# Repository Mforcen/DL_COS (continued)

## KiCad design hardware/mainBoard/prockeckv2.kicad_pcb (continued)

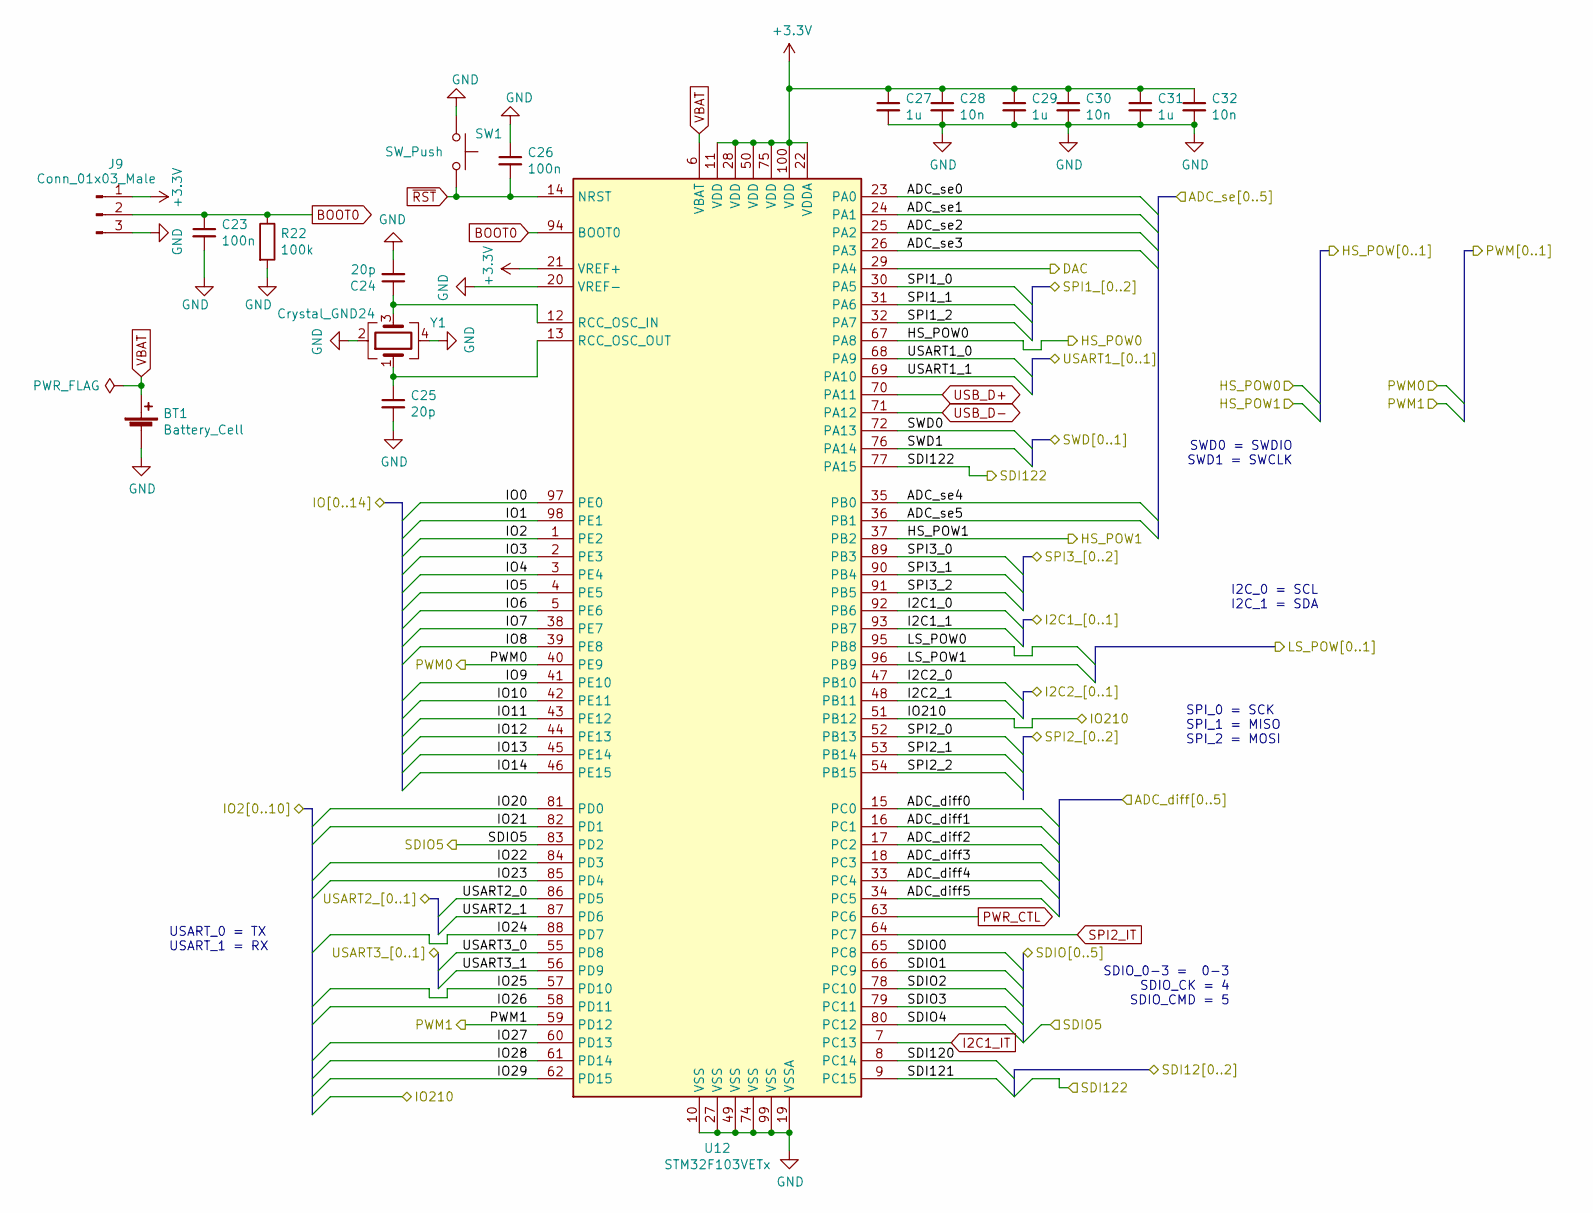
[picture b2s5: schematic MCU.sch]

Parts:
BT1: Battery_Cell; BT-CR2032
C23, C26: 100n; C_0603_1608Metric_Pad1.05x0.95mm_HandSolder
C24, C25: 20p; C_0603_1608Metric_Pad1.05x0.95mm_HandSolder
C27, C29, C31: 1u; C_0603_1608Metric_Pad1.05x0.95mm_HandSolder
C28, C30, C32: 10n; C_0603_1608Metric_Pad1.05x0.95mm_HandSolder
J9: Conn_01x03_Male; PinSocket_1x03_P2.54mm_Vertical
R22: 100k; R_0603_1608Metric_Pad1.05x0.95mm_HandSolder
SW1: SW_Push; SW_PUSH_6mm_H4.3mm
U12: STM32F103VETx; LQFP-100_14x14mm_P0.5mm
Y1: Crystal_GND24; Crystal_SMD_7050-4Pin_7.0x5.0mm

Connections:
/Analog Conditioning/ADC_se0: U12.23 (PA0); also elsewhere on the board
/Analog Conditioning/ADC_se1: U12.24 (PA1); also elsewhere on the board
/Analog Conditioning/ADC_se2: U12.25 (PA2); also elsewhere on the board
/Analog Conditioning/ADC_se3: U12.26 (PA3); also elsewhere on the board
/Analog Conditioning/ADC_se4: U12.35 (PB0); also elsewhere on the board
/Analog Conditioning/ADC_se5: U12.36 (PB1); also elsewhere on the board
/Controlled Power/LS_POW0: U12.95 (PB8); also elsewhere on the board
/Controlled Power/LS_POW1: U12.96 (PB9); also elsewhere on the board
/DifferentialConditioning.sch/ADC_diff0: U12.15 (PC0); also elsewhere on the board
/DifferentialConditioning.sch/ADC_diff1: U12.16 (PC1); also elsewhere on the board
/DifferentialConditioning.sch/ADC_diff2: U12.17 (PC2); also elsewhere on the board
/DifferentialConditioning.sch/ADC_diff3: U12.18 (PC3); also elsewhere on the board
/DifferentialConditioning.sch/ADC_diff4: U12.33 (PC4); also elsewhere on the board
/DifferentialConditioning.sch/ADC_diff5: U12.34 (PC5); also elsewhere on the board
/External Connections/I2C1_0: U12.92 (PB6); also elsewhere on the board
/External Connections/I2C1_1: U12.93 (PB7); also elsewhere on the board
/External Connections/I2C2_0: U12.47 (PB10); also elsewhere on the board
/External Connections/I2C2_1: U12.48 (PB11); also elsewhere on the board
/External Connections/SPI2_0: U12.52 (PB13); also elsewhere on the board
/External Connections/SPI2_1: U12.53 (PB14); also elsewhere on the board
/External Connections/SPI2_2: U12.54 (PB15); also elsewhere on the board
/External Connections/SPI3_0: U12.89 (PB3); also elsewhere on the board
/External Connections/SPI3_1: U12.90 (PB4); also elsewhere on the board
/External Connections/SPI3_2: U12.91 (PB5); also elsewhere on the board
/External Connections/SWD0: U12.72 (PA13); also elsewhere on the board
/External Connections/SWD1: U12.76 (PA14); also elsewhere on the board
/External Connections/USART1_0: U12.68 (PA9); also elsewhere on the board
/External Connections/USART1_1: U12.69 (PA10); also elsewhere on the board
/External Connections/USART2_0: U12.86 (PD5); also elsewhere on the board
/External Connections/USART2_1: U12.87 (PD6); also elsewhere on the board
/External Connections/USART3_0: U12.55 (PD8); also elsewhere on the board
/External Connections/USART3_1: U12.56 (PD9); also elsewhere on the board
/IO/DAC: U12.29 (PA4); also elsewhere on the board
/IO/IO0: U12.97 (PE0); also elsewhere on the board
/IO/IO1: U12.98 (PE1); also elsewhere on the board
/IO/IO2: U12.1 (PE2); also elsewhere on the board
/IO/IO3: U12.2 (PE3); also elsewhere on the board
/IO/IO4: U12.3 (PE4); also elsewhere on the board
/IO/IO5: U12.4 (PE5); also elsewhere on the board
/IO/IO6: U12.5 (PE6); also elsewhere on the board
/IO/IO7: U12.38 (PE7); also elsewhere on the board
/IO/IO8: U12.39 (PE8); also elsewhere on the board
/IO/IO9: U12.41 (PE10); also elsewhere on the board
/IO/IO10: U12.42 (PE11); also elsewhere on the board
/IO/IO11: U12.43 (PE12); also elsewhere on the board
/IO/IO12: U12.44 (PE13); also elsewhere on the board
/IO/IO13: U12.45 (PE14); also elsewhere on the board
/IO/IO14: U12.46 (PE15); also elsewhere on the board
/MCU/HS_POW0: U12.67 (PA8); also elsewhere on the board
/MCU/HS_POW1: U12.37 (PB2); also elsewhere on the board
/MCU/IO20: U12.81 (PD0); also elsewhere on the board
/MCU/IO21: U12.82 (PD1); also elsewhere on the board
/MCU/IO22: U12.84 (PD3); also elsewhere on the board
/MCU/IO23: U12.85 (PD4); also elsewhere on the board
/MCU/IO24: U12.88 (PD7); also elsewhere on the board
/MCU/IO25: U12.57 (PD10); also elsewhere on the board
/MCU/IO26: U12.58 (PD11); also elsewhere on the board
/MCU/IO27: U12.60 (PD13); also elsewhere on the board
/MCU/IO28: U12.61 (PD14); also elsewhere on the board
/MCU/IO29: U12.62 (PD15); also elsewhere on the board
/MCU/IO210: U12.51 (PB12); also elsewhere on the board
/MCU/PWM0: U12.40 (PE9); also elsewhere on the board
/MCU/PWM1: U12.59 (PD12); also elsewhere on the board
/MCU/SDI120: U12.8 (PC14); also elsewhere on the board
/MCU/SDI121: U12.9 (PC15); also elsewhere on the board
/MCU/SDI122: U12.77 (PA15); also elsewhere on the board
/MCU/SDIO0: U12.65 (PC8); also elsewhere on the board
/MCU/SDIO1: U12.66 (PC9); also elsewhere on the board
/MCU/SDIO2: U12.78 (PC10); also elsewhere on the board
/MCU/SDIO3: U12.79 (PC11); also elsewhere on the board
/MCU/SDIO4: U12.80 (PC12); also elsewhere on the board
/MCU/SDIO5: U12.83 (PD2); also elsewhere on the board
/MCU/SPI1_0: U12.30 (PA5); also elsewhere on the board
/MCU/SPI1_1: U12.31 (PA6); also elsewhere on the board
/MCU/SPI1_2: U12.32 (PA7); also elsewhere on the board
BOOT0: C23.1, J9.2, R22.1, U12.94 (BOOT0); also elsewhere on the board
GND: BT1.2 (-), C23.2, C24.2, C25.2, C26.1, C27.2, C28.2, C29.2, C30.2, C31.2, C32.2, J9.3, R22.2, SW1.1, U12.10 (VSS), U12.19 (VSSA), U12.20 (VREF-), U12.27 (VSS), U12.49 (VSS), U12.74 (VSS), U12.99 (VSS), Y1.2, Y1.4; also elsewhere on the board
I2C1_IT: U12.7 (PC13); also elsewhere on the board
unnamed: C24.1, U12.12 (RCC_OSC_IN), Y1.3
unnamed: C25.1, U12.13 (RCC_OSC_OUT), Y1.1
PWR_CTL: U12.63 (PC6); also elsewhere on the board
SPI2_IT: U12.64 (PC7); also elsewhere on the board
USB_D+: U12.70 (PA11); also elsewhere on the board
USB_D-: U12.71 (PA12); also elsewhere on the board
VBAT: BT1.1 (+), U12.6 (VBAT)
~RST: C26.2, SW1.2, U12.14 (NRST); also elsewhere on the board

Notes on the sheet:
USART_0 = TX USART_1 = RX
I2C_0 = SCL I2C_1 = SDA
SPI_0 = SCK SPI_1 = MISO SPI_2 = MOSI
SDIO_0-3 = 0-3 SDIO_CK = 4 SDIO_CMD = 5
SWD0 = SWDIO SWD1 = SWCLK

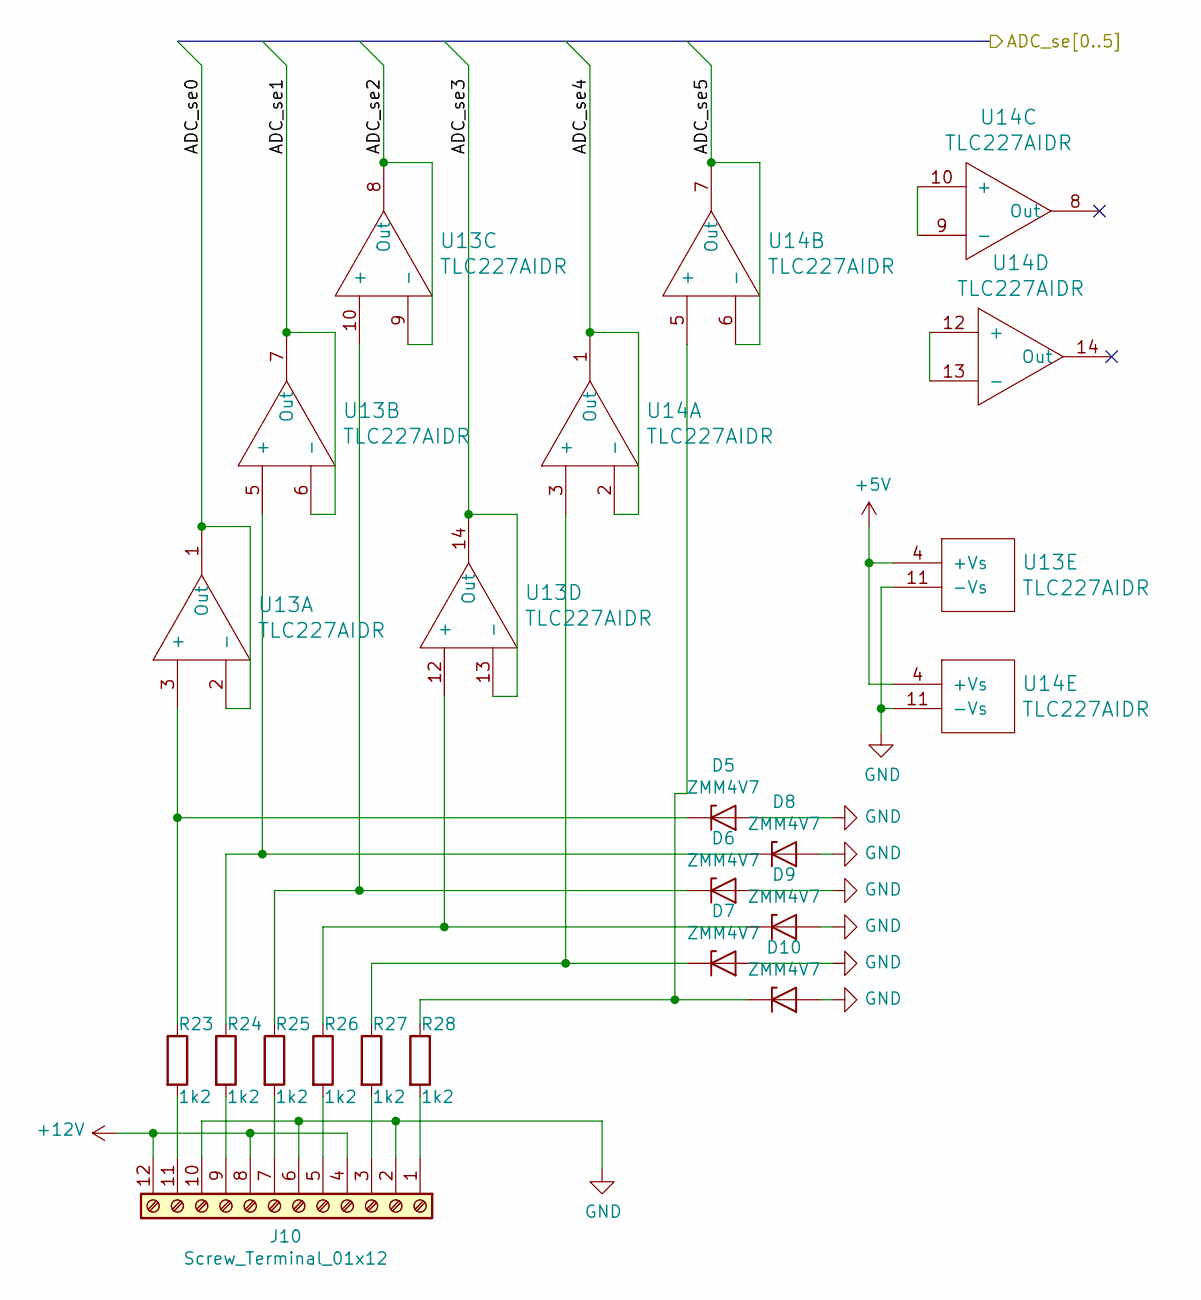
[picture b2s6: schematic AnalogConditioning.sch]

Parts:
D5, D6, D7, D8, D9, D10: ZMM4V7; D_MiniMELF
J10: Screw_Terminal_01x12; TerminalBlock_12_P5.08mm
R23, R24, R25, R26, R27, R28: 1k2; R_0603_1608Metric_Pad1.05x0.95mm_HandSolder
U13, U14: TLC227AIDR; SOIC-14_3.9x8.7mm_P1.27mm

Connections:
+5V: U13.4 (+Vs), U14.4 (+Vs); also elsewhere on the board
+12V: J10.4, J10.8, J10.12; also elsewhere on the board
/Analog Conditioning/ADC_se0: U13.1 (Out), U13.2 (-); also elsewhere on the board
/Analog Conditioning/ADC_se1: U13.6 (-), U13.7 (Out); also elsewhere on the board
/Analog Conditioning/ADC_se2: U13.8 (Out), U13.9 (-); also elsewhere on the board
/Analog Conditioning/ADC_se3: U13.13 (-), U13.14 (Out); also elsewhere on the board
/Analog Conditioning/ADC_se4: U14.1 (Out), U14.2 (-); also elsewhere on the board
/Analog Conditioning/ADC_se5: U14.6 (-), U14.7 (Out); also elsewhere on the board
GND: D5.2 (A), D6.2 (A), D7.2 (A), D8.2 (A), D9.2 (A), D10.2 (A), J10.2, J10.6, J10.10, U13.11 (-Vs), U14.11 (-Vs); also elsewhere on the board
unnamed: D5.1 (K), R23.1, U13.3 (+)
unnamed: D6.1 (K), R25.1, U13.10 (+)
unnamed: D7.1 (K), R27.1, U14.3 (+)
unnamed: D8.1 (K), R24.1, U13.5 (+)
unnamed: D9.1 (K), R26.1, U13.12 (+)
unnamed: D10.1 (K), R28.1, U14.5 (+)
unnamed: J10.1, R28.2
unnamed: J10.3, R27.2
unnamed: J10.5, R26.2
unnamed: J10.7, R25.2
unnamed: J10.9, R24.2
unnamed: J10.11, R23.2
unnamed: U14.9 (-), U14.10 (+)
unnamed: U14.12 (+), U14.13 (-)

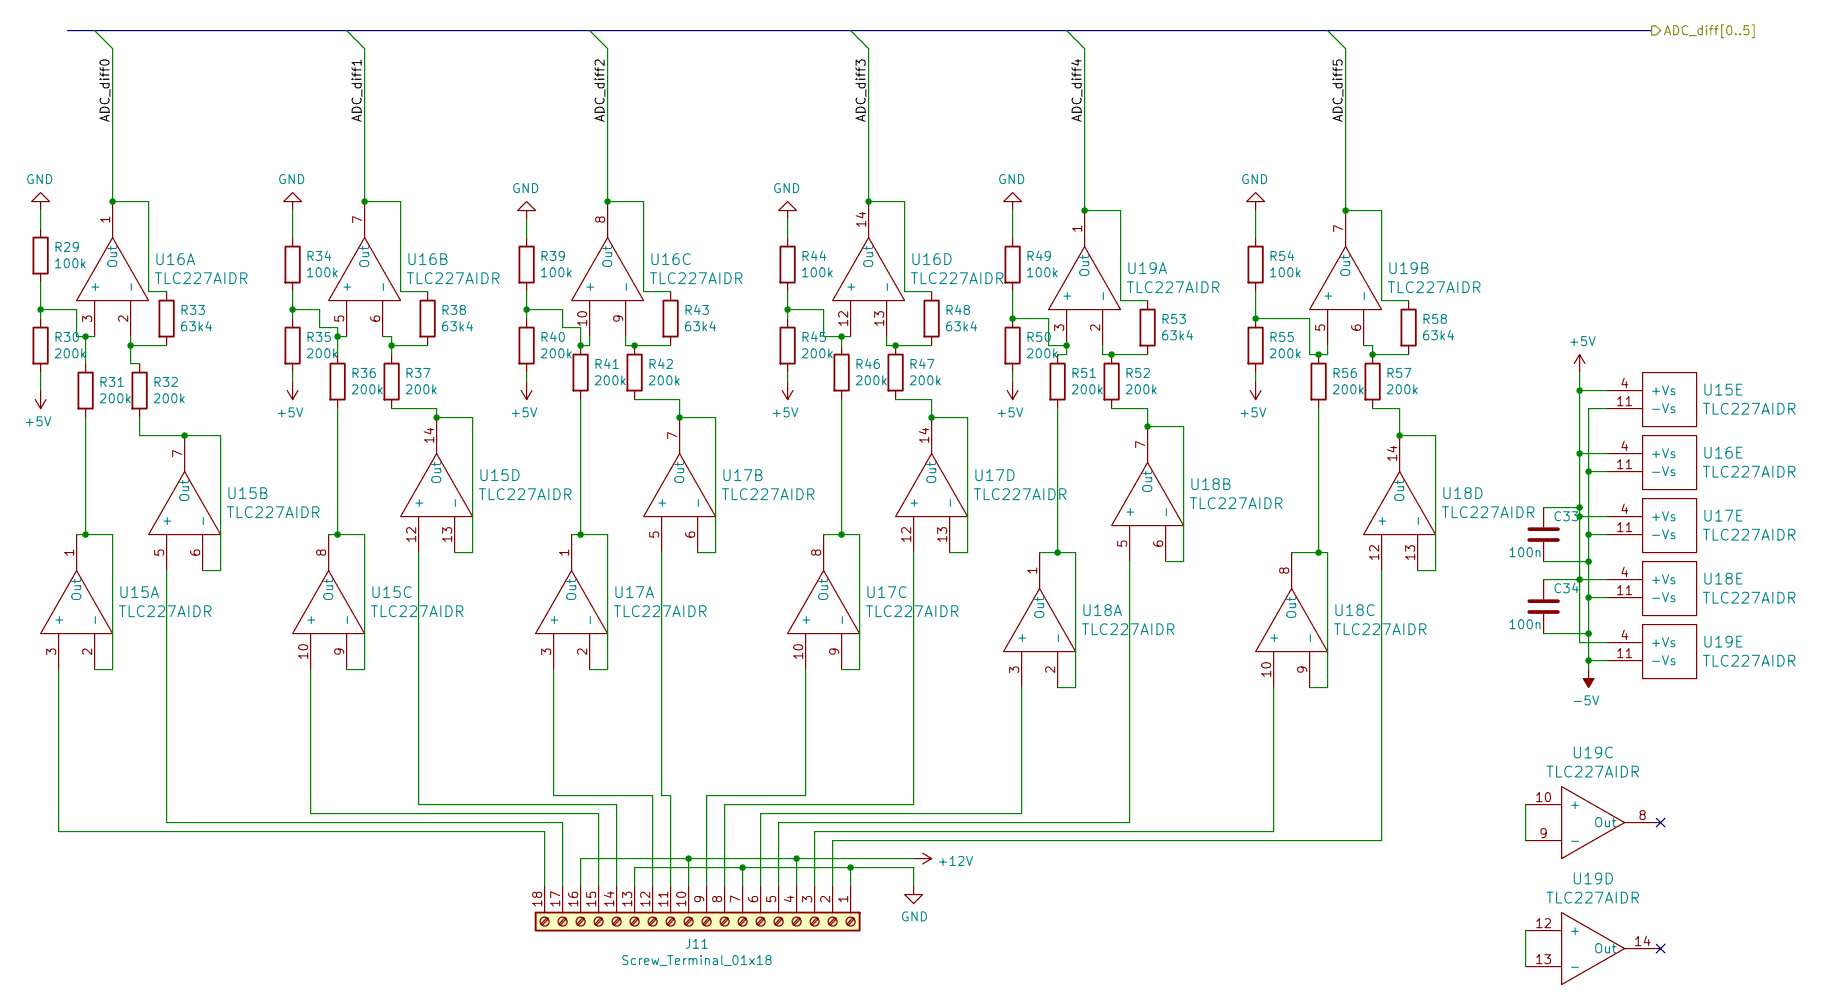
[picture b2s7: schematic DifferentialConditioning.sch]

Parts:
C33, C34: 100n; C_0603_1608Metric_Pad1.05x0.95mm_HandSolder
J11: Screw_Terminal_01x18; TerminalBlock_18_P5.08mm
R29, R34, R39, R44, R49, R54: 100k; R_0603_1608Metric_Pad1.05x0.95mm_HandSolder
R30, R31, R32, R35, R36, R37, R40, R41, R42, R45, R46, R47, R50, R51, R52, R55, R56, R57: 200k; R_0603_1608Metric_Pad1.05x0.95mm_HandSolder
R33, R38, R43, R48, R53, R58: 63k4; R_0603_1608Metric_Pad1.05x0.95mm_HandSolder
U15, U16, U17, U18, U19: TLC227AIDR; SOIC-14_3.9x8.7mm_P1.27mm

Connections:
+5V: C33.1, C34.1, R30.2, R35.2, R40.2, R45.2, R50.2, R55.2, U15.4 (+Vs), U16.4 (+Vs), U17.4 (+Vs), U18.4 (+Vs), U19.4 (+Vs); also elsewhere on the board
+12V: J11.4, J11.10, J11.16; also elsewhere on the board
-5V: C33.2, C34.2, U15.11 (-Vs), U16.11 (-Vs), U17.11 (-Vs), U18.11 (-Vs), U19.11 (-Vs); also elsewhere on the board
/DifferentialConditioning.sch/ADC_diff0: R33.1, U16.1 (Out); also elsewhere on the board
/DifferentialConditioning.sch/ADC_diff1: R38.1, U16.7 (Out); also elsewhere on the board
/DifferentialConditioning.sch/ADC_diff2: R43.1, U16.8 (Out); also elsewhere on the board
/DifferentialConditioning.sch/ADC_diff3: R48.1, U16.14 (Out); also elsewhere on the board
/DifferentialConditioning.sch/ADC_diff4: R53.1, U19.1 (Out); also elsewhere on the board
/DifferentialConditioning.sch/ADC_diff5: R58.1, U19.7 (Out); also elsewhere on the board
GND: J11.1, J11.7, J11.13, R29.1, R34.1, R39.1, R44.1, R49.1, R54.1; also elsewhere on the board
unnamed: J11.2, U18.12 (+)
unnamed: J11.3, U18.10 (+)
unnamed: J11.5, U18.5 (+)
unnamed: J11.6, U18.3 (+)
unnamed: J11.8, U17.12 (+)
unnamed: J11.9, U17.10 (+)
unnamed: J11.11, U17.5 (+)
unnamed: J11.12, U17.3 (+)
unnamed: J11.14, U15.12 (+)
unnamed: J11.15, U15.10 (+)
unnamed: J11.17, U15.5 (+)
unnamed: J11.18, U15.3 (+)
unnamed: R29.2, R30.1, R31.1, U16.3 (+)
unnamed: R31.2, U15.1 (Out), U15.2 (-)
unnamed: R32.1, R33.2, U16.2 (-)
unnamed: R32.2, U15.6 (-), U15.7 (Out)
unnamed: R34.2, R35.1, R36.1, U16.5 (+)
unnamed: R36.2, U15.8 (Out), U15.9 (-)
unnamed: R37.1, R38.2, U16.6 (-)
unnamed: R37.2, U15.13 (-), U15.14 (Out)
unnamed: R39.2, R40.1, R41.1, U16.10 (+)
unnamed: R41.2, U17.1 (Out), U17.2 (-)
unnamed: R42.1, R43.2, U16.9 (-)
unnamed: R42.2, U17.6 (-), U17.7 (Out)
unnamed: R44.2, R45.1, R46.1, U16.12 (+)
unnamed: R46.2, U17.8 (Out), U17.9 (-)
unnamed: R47.1, R48.2, U16.13 (-)
unnamed: R47.2, U17.13 (-), U17.14 (Out)
unnamed: R49.2, R50.1, R51.1, U19.3 (+)
unnamed: R51.2, U18.1 (Out), U18.2 (-)
unnamed: R52.1, R53.2, U19.2 (-)
unnamed: R52.2, U18.6 (-), U18.7 (Out)
unnamed: R54.2, R55.1, R56.1, U19.5 (+)
unnamed: R56.2, U18.8 (Out), U18.9 (-)
unnamed: R57.1, R58.2, U19.6 (-)
unnamed: R57.2, U18.13 (-), U18.14 (Out)
unnamed: U19.9 (-), U19.10 (+)
unnamed: U19.12 (+), U19.13 (-)

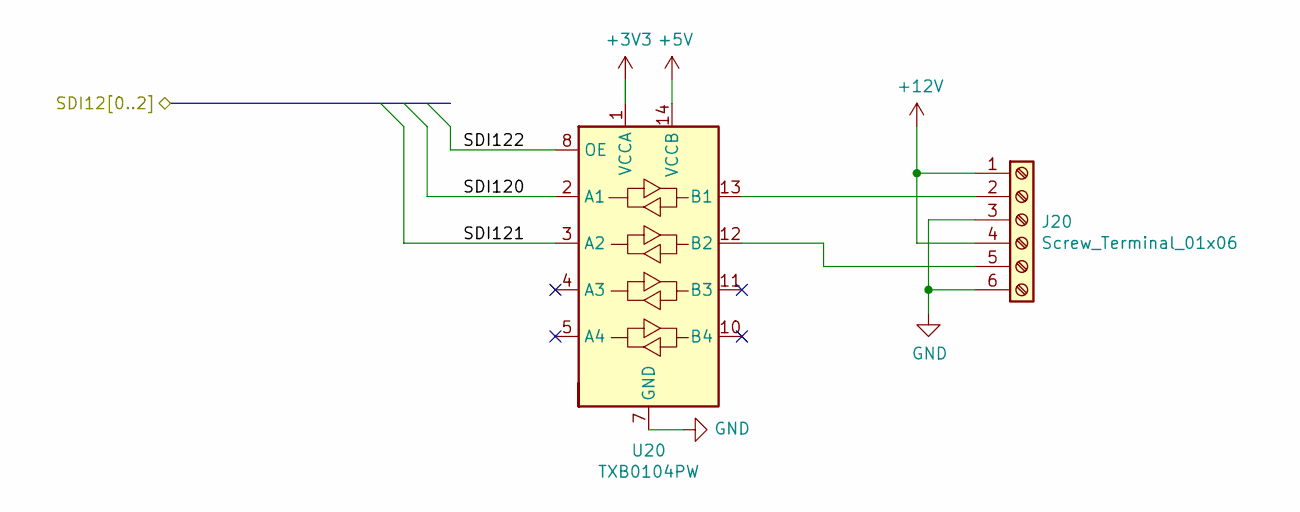
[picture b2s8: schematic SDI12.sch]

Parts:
J20: Screw_Terminal_01x06; TerminalBlock_bornier-6_P5.08mm
U20: TXB0104PW; TSSOP-14_4.4x5mm_P0.65mm

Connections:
+5V: U20.14 (VCCB); also elsewhere on the board
+12V: J20.1, J20.4; also elsewhere on the board
/MCU/SDI120: U20.2 (A1); also elsewhere on the board
/MCU/SDI121: U20.3 (A2); also elsewhere on the board
/MCU/SDI122: U20.8 (OE); also elsewhere on the board
GND: J20.3, J20.6, U20.7 (GND); also elsewhere on the board
unnamed: J20.2, U20.13 (B1)
unnamed: J20.5, U20.12 (B2)

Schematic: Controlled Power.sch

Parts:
F1, F2, F3, F4: SL1210400; R_1210_3225Metric
J21, J22, J23, J24: Screw_Terminal_01x02; PinHeader_1x02_P2.54mm_Vertical
Q4, Q5: S8050; SOT-23_Handsoldering
Q6, Q7: AO3415; SOT-23_Handsoldering
Q8, Q9: AP2300; SOT-23_Handsoldering
R59, R60, R61, R62: 100k; R_0603_1608Metric_Pad1.05x0.95mm_HandSolder
R63, R64: 10k; R_0603_1608Metric_Pad1.05x0.95mm_HandSolder
R65, R66: 1M; R_0603_1608Metric_Pad1.05x0.95mm_HandSolder

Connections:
+12V: F1.1, F2.1, J23.1, J24.1, R61.2, R62.2; also elsewhere on the board
/Controlled Power/LS_POW0: R63.2; also elsewhere on the board
/Controlled Power/LS_POW1: R64.2; also elsewhere on the board
/MCU/HS_POW0: R59.2; also elsewhere on the board
/MCU/HS_POW1: R60.2; also elsewhere on the board
GND: J21.2, J22.2, Q4.2 (E), Q5.2 (E), Q8.3 (D), Q9.3 (D), R65.1, R66.1; also elsewhere on the board
unnamed: F1.2, Q6.2 (S)
unnamed: F2.2, Q7.2 (S)
unnamed: F3.1, J23.2
unnamed: F3.2, Q8.2 (S)
unnamed: F4.1, J24.2
unnamed: F4.2, Q9.2 (S)
unnamed: J21.1, Q6.3 (D)
unnamed: J22.1, Q7.3 (D)
unnamed: Q4.1 (B), R59.1
unnamed: Q4.3 (C), Q6.1 (G), R61.1
unnamed: Q5.1 (B), R60.1
unnamed: Q5.3 (C), Q7.1 (G), R62.1
unnamed: Q8.1 (G), R63.1, R65.2
unnamed: Q9.1 (G), R64.1, R66.2

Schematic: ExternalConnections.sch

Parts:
J12, J13, J14, J15: Conn_01x04_Male; JST_EH_B4B-EH-A_1x04_P2.50mm_Vertical
J16, J18: Conn_01x05_Male; JST_EH_B5B-EH-A_1x05_P2.50mm_Vertical
J17, J19: Conn_01x06_Male; JST_EH_B6B-EH-A_1x06_P2.50mm_Vertical

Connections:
/External Connections/I2C1_0: J16.2; also elsewhere on the board
/External Connections/I2C1_1: J16.3; also elsewhere on the board
/External Connections/I2C2_0: J15.2; also elsewhere on the board
/External Connections/I2C2_1: J15.3; also elsewhere on the board
/External Connections/SPI2_0: J17.2; also elsewhere on the board
/External Connections/SPI2_1: J17.3; also elsewhere on the board
/External Connections/SPI2_2: J17.4; also elsewhere on the board
/External Connections/SPI3_0: J18.2; also elsewhere on the board
/External Connections/SPI3_1: J18.3; also elsewhere on the board
/External Connections/SPI3_2: J18.4; also elsewhere on the board
/External Connections/SWD0: J19.2; also elsewhere on the board
/External Connections/SWD1: J19.3; also elsewhere on the board
/External Connections/USART1_0: J12.2; also elsewhere on the board
/External Connections/USART1_1: J12.3; also elsewhere on the board
/External Connections/USART2_0: J13.2; also elsewhere on the board
/External Connections/USART2_1: J13.3; also elsewhere on the board
/External Connections/USART3_0: J14.2; also elsewhere on the board
/External Connections/USART3_1: J14.3; also elsewhere on the board
BOOT0: J19.4; also elsewhere on the board
GND: J12.4, J13.4, J14.4, J15.4, J16.5, J17.6, J18.5, J19.6; also elsewhere on the board
I2C1_IT: J16.4; also elsewhere on the board
SPI2_IT: J17.5; also elsewhere on the board
~RST: J19.5; also elsewhere on the board

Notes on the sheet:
I2C_0 = SCL I2C_1 = SDA
USART_0 = TX USART_1 = RX
SPI_0 = SCK SPI_1 = MISO SPI_2 = MOSI
SWD0 = SWDIO SWD1 = SWCLK

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
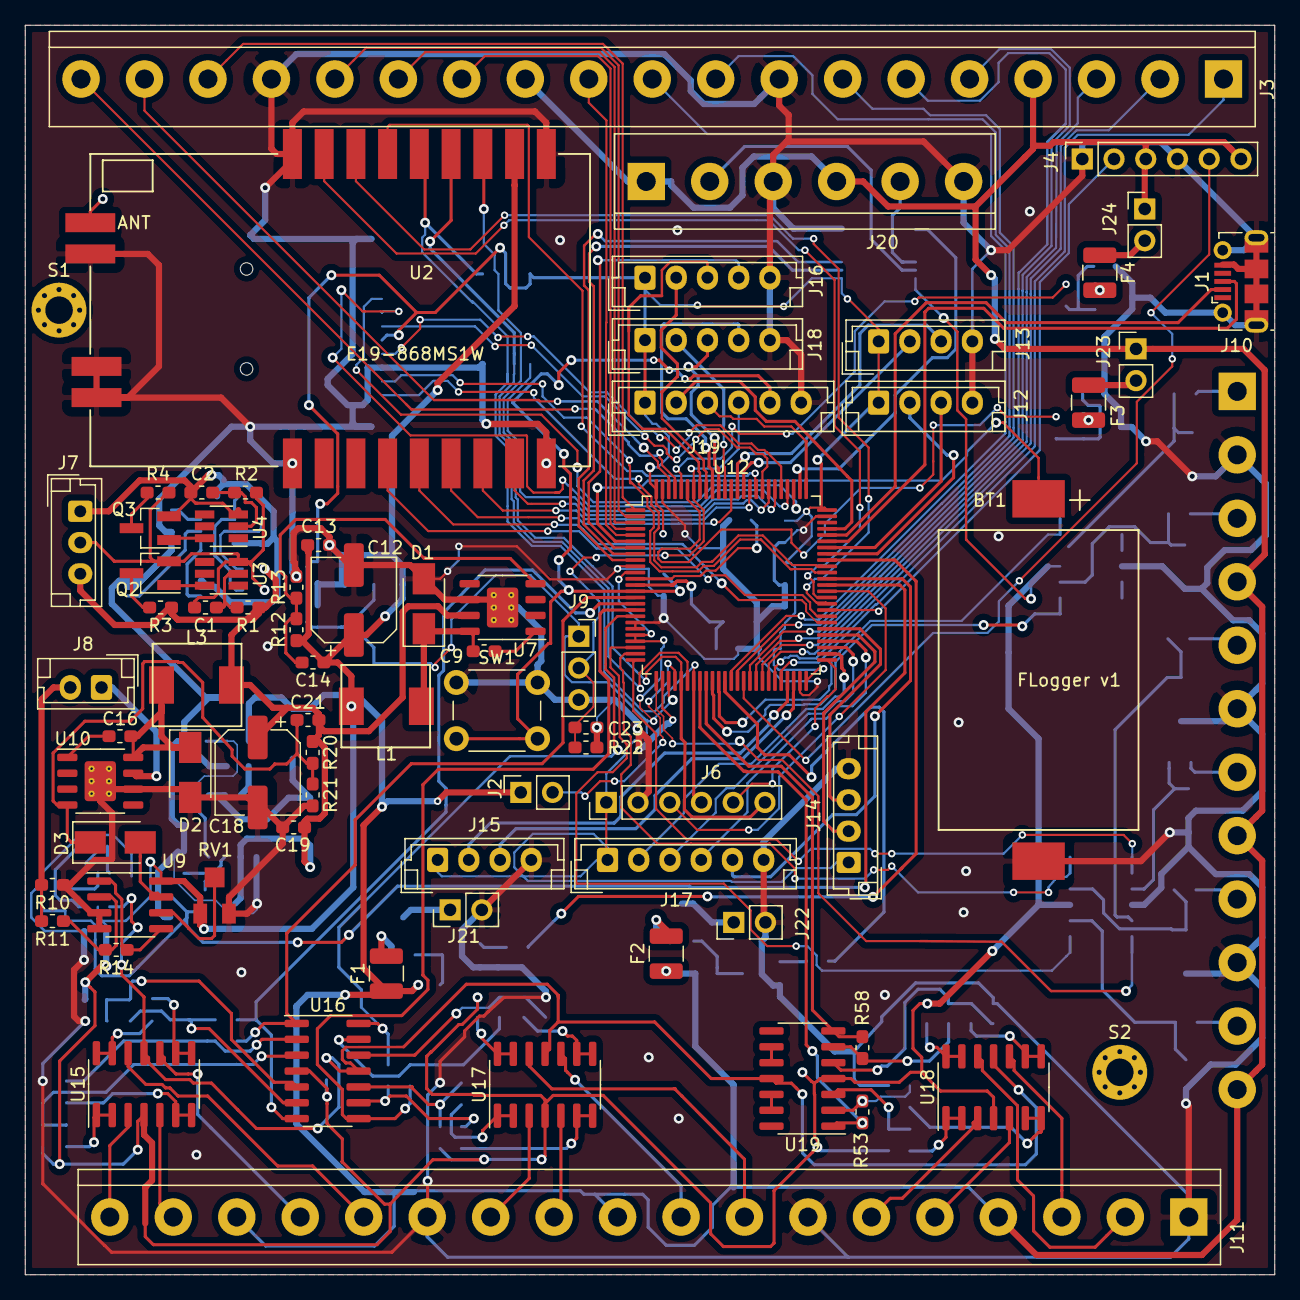
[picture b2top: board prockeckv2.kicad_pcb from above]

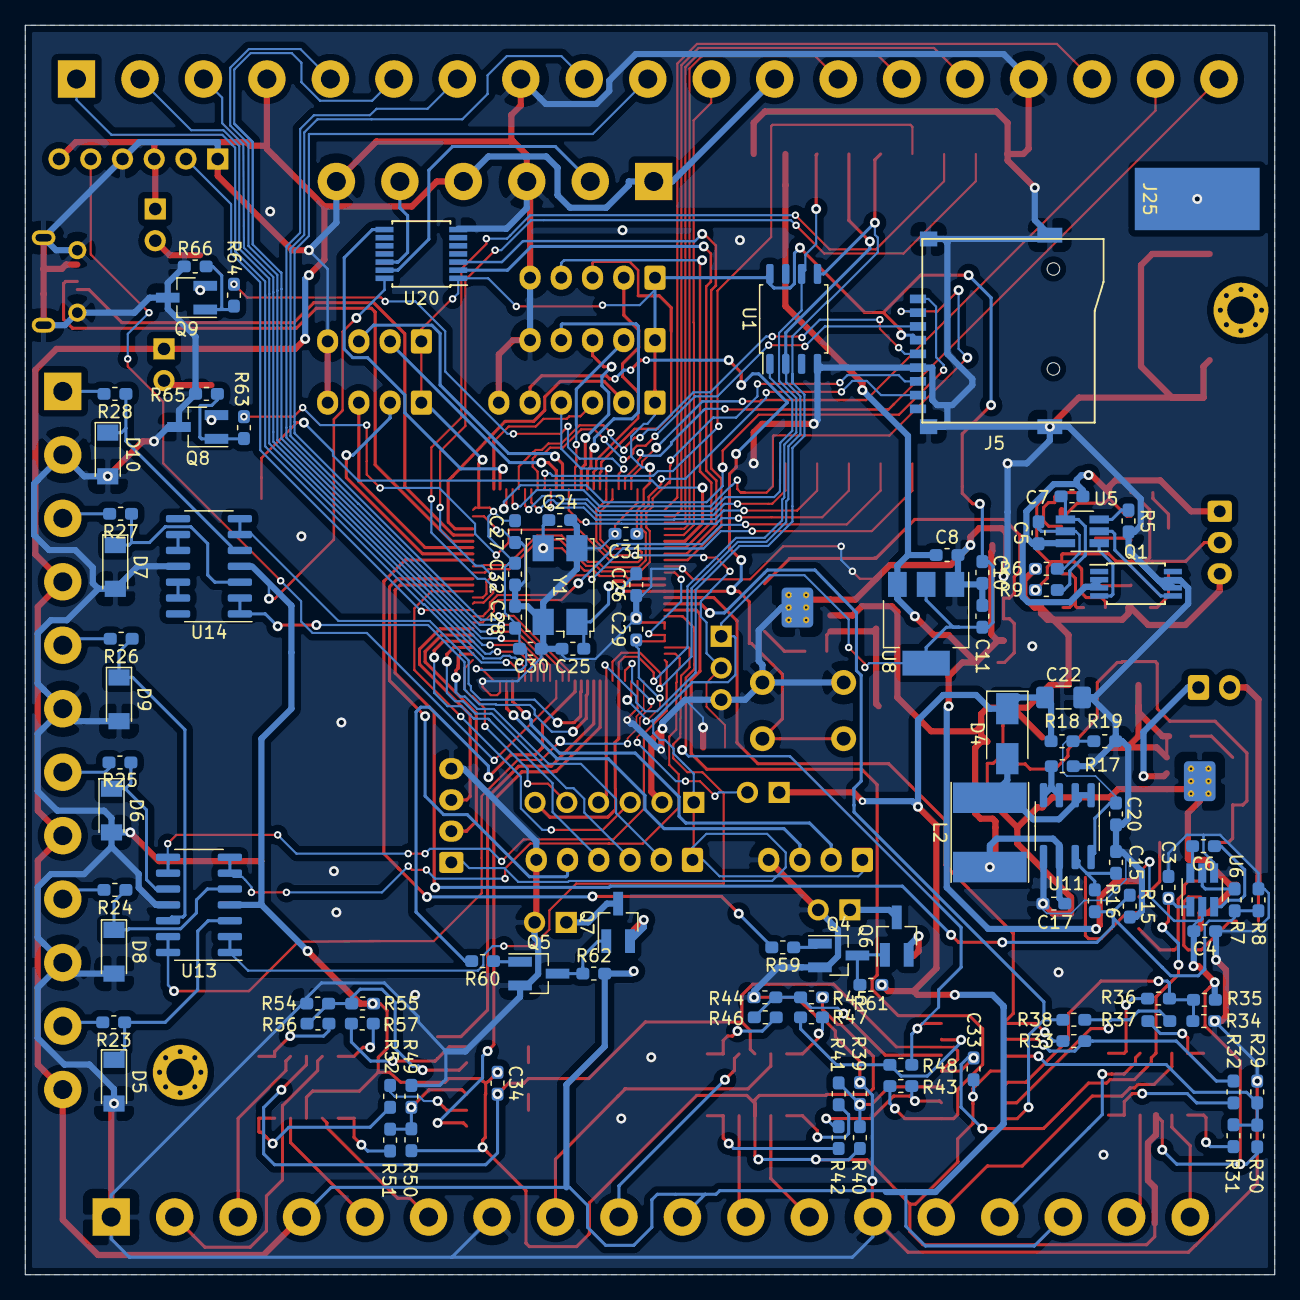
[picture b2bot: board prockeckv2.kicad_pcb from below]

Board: 2 copper layers, 100.0 x 100.0 mm, 177 parts (101 on the bottom side), 192 nets.

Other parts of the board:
S1, S2: MountingHole_2.2mm_M2_Pad_Via

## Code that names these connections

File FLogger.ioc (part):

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Mcu.Name=STM32F103R(C-D-E)Tx
Mcu.Package=LQFP64
Mcu.UserName=STM32F103RETx
PA0-WKUP.Signal=ADCx_IN0
PA1.Signal=ADCx_IN1
PA10.Mode=Asynchronous
PA10.Signal=USART1_RX
PA11.Mode=Device
PA11.Signal=USB_DM
PA12.Mode=Device
PA12.Signal=USB_DP
PA13.Mode=Serial_Wire
PA13.Signal=SYS_JTMS-SWDIO
PA14.Mode=Serial_Wire
PA14.Signal=SYS_JTCK-SWCLK
PA15.GPIOParameters=GPIO_Label
PA15.GPIO_Label=Flash_nss
PA15.Signal=GPIO_Output
PA2.Signal=ADCx_IN2
PA3.Signal=ADCx_IN3
PA4.Signal=ADCx_IN4
PA5.Signal=COMP_DAC2_group
PA6.Signal=GPIO_Output
PA7.GPIOParameters=GPIO_Label
PA7.GPIO_Label=Radio_rst
PA7.Signal=GPIO_Output
PA8.GPIOParameters=GPIO_Label
PA8.GPIO_Label=SDI12_Dir
PA8.Signal=GPIO_Output
PA9.Mode=Asynchronous
PA9.Signal=USART1_TX
PB0.GPIOParameters=GPIO_Label
PB0.GPIO_Label=Radio_dio0
PB0.Signal=GPIO_Input
PB1.GPIOParameters=GPIO_Label
PB1.GPIO_Label=Radio_dio1
PB1.Signal=GPIO_Input
PB10.Mode=SMBus-Alert-mode
PB10.Signal=I2C2_SCL
PB11.Mode=SMBus-Alert-mode
PB11.Signal=I2C2_SDA
PB12.Mode=SMBus-Alert-mode
PB12.Signal=I2C2_SMBA
PB13.Mode=Full_Duplex_Master
PB13.Signal=SPI2_SCK
PB14.Mode=Full_Duplex_Master
PB14.Signal=SPI2_MISO
PB15.Mode=Full_Duplex_Master
PB15.Signal=SPI2_MOSI
PB2.Signal=GPIO_Output
PB3.Mode=Full_Duplex_Master
PB3.Signal=SPI1_SCK
PB4.Mode=Full_Duplex_Master
PB4.Signal=SPI1_MISO
PB5.Mode=Full_Duplex_Master
PB5.Signal=SPI1_MOSI
PB6.Mode=I2C
PB6.Signal=I2C1_SCL
PB7.Mode=I2C
PB7.Signal=I2C1_SDA
PB8.GPIOParameters=GPIO_Label
PB8.GPIO_Label=Radio_nss
PB8.Signal=GPIO_Output
PB9.GPIOParameters=GPIO_Label
PB9.GPIO_Label=SPI2_NSS
PB9.Signal=GPIO_Output
PC0.Signal=GPIO_Output
PC1.Signal=GPIO_Output
PC10.Mode=Asynchronous
PC10.Signal=USART3_TX
PC11.Mode=Asynchronous
PC11.Signal=USART3_RX
PC12.Mode=SD_1_bit
PC12.Signal=SDIO_CK
PC14-OSC32_IN.Mode=LSE-External-Oscillator
PC14-OSC32_IN.Signal=RCC_OSC32_IN
PC15-OSC32_OUT.Mode=LSE-External-Oscillator
PC15-OSC32_OUT.Signal=RCC_OSC32_OUT
PC2.Signal=GPIO_Output
PC3.Signal=GPIO_Output
PC4.GPIOParameters=GPIO_Label
PC4.GPIO_Label=Radio_rxen
PC4.Signal=GPIO_Output
PC5.GPIOParameters=GPIO_Label
PC5.GPIO_Label=Radio_txen
PC5.Signal=GPIO_Output
PC6.GPIOParameters=GPIO_Label
PC6.GPIO_Label=SDI12_0
PC6.Signal=GPIO_Output
PC7.GPIOParameters=GPIO_Label
PC7.GPIO_Label=SDI12_1
PC7.Signal=GPIO_Output
PC8.Mode=SD_1_bit
PC8.Signal=SDIO_D0
PC9.GPIOParameters=GPIO_Label
PC9.GPIO_Label=SDIO_CD
PC9.Signal=GPIO_Input
PD0-OSC_IN.Mode=HSE-External-Oscillator
PD0-OSC_IN.Signal=RCC_OSC_IN
PD1-OSC_OUT.Mode=HSE-External-Oscillator
PD1-OSC_OUT.Signal=RCC_OSC_OUT
PD2.Mode=SD_1_bit
PD2.Signal=SDIO_CMD
RCC.SYSCLKFreq_VALUE=72000000
RCC.SYSCLKSource=RCC_SYSCLKSOURCE_PLLCLK
board=custom

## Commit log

2019-11-13 Added hardware definitions
2019-11-13 initial commit of board
2019-12-07 Added the power part of the schematic
2019-12-09 Added external connections, analog conditioning and several items
2019-12-11 Ended schematic, created some pcb footprints
2019-12-13 PCB finished
2020-01-23 First working software
2020-02-09 Major changes: - Added a mutex-like hardware peripheral for SPI - WIP in Flash driver - Removed build files - Added CPP ABI files for virtual functions - Added an untested SDI12 driver
2020-03-17 Barely working SDI12 and LoRa drivers
2020-04-22 Added Virtual Machine to OS Added support for files to File System Added task scheduler to main loop.
2020-04-27 Working Virtual Machine
2020-05-03 Added RTC support, fixed some memory allocation problems in eTSDB file system
2020-05-12 Logging to flash fully working now by copying the row into eTSDB driver.
    Cleanup of unused code.
    Modified control.py in order to allow args without value.
    Several fixes.
2020-05-14 Added functions to retrieve parsed data from flash Added a logging class
2020-05-22 LoRa driver can receive packets now Added a SSD1306 I2C screen driver.
    Some minor fixes.
2020-05-28 Fixed a bug in SDI12 driver
2020-07-20 Changed board. SDI12 fully working now. Added binary serial communications.
2020-07-28 First version of LinkLayer
2020-08-05 Working LinkLayer driver
2020-08-21 New version of PCB, several bugs fixed
2020-08-26 First fully working version.
    Improved file system to allow more columns in tables.
    Added a vector class to mem_structs.
    Added memory move capabilities to some memory structs.
    Fully working SDI12 driver.
    Updated PCB.
2020-09-04 First fully working version
    eTSDB updated with unlimited number of columns.
    SDI12 fully implemented.
    Virtual machine fully working.
    Log is now capable to change FD.
    Dynamic vector is added to mem structs.
2020-09-15 New PCB, some minor fixes
2020-11-17 Added USB support Added Port and Socket abstraction classes Added simple HTTP support through GSM Added a kernel level message queue
    KVS module setting system
    LoRa variable refactoring
2020-11-26 New board version Fully working version with SIM800
2020-12-03 Improved ISRs to be faster Changed ownership from uintptr_t to void* Added Context object to VM Improved GSM driver
2020-12-18 Improved logging capabilities Added TODOs to improve the firmware Fixed ADCs Added functions to get battery information
2020-12-23 Added VRefint support
2021-01-25 Added dual build capabilities and bug fixed
2021-01-29 Embedded program is now an external file, which makes easier to generate images through scripting
2021-02-03 SDI12 driver only allowed to read address 0, GSM Driver checks network registration before open bearer
2021-02-15 WDT added, W25N01GV Driver added
2021-02-16 Cleanup of old code, added SFS
2021-02-16 Maintenance release, removed unused code
2021-02-16 Removed unused code
2021-02-16 Added flash test command
2021-02-16 RTC Second IT added, IWDG working
2021-02-17 Added periodic alarms to feed wdt and check alarms
2021-02-17 Added HTTPAction check, fixed SDI12_Driver log
2021-02-18 Improved RTC alarm system storing full timestamp
2021-02-18 Reduced verbosity on SDI12 driver, added gen_programs script
2021-02-18 Increased timeouts to avoid httpaction errors
2021-02-18 Improved error handling in HTTPAction error
2021-02-19 Fixed error code handling in GSM driver
2021-02-19 Updated GSM Driver to not output response from server
2021-02-21 Changed RTC clock to LSI
2021-07-29 Major cleanup, leaving one architecture only
2021-07-29 Added documentation Several bug fixes
